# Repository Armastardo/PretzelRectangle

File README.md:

# PretzelRectangle
Custom rectangle PCB for PretzelGuy

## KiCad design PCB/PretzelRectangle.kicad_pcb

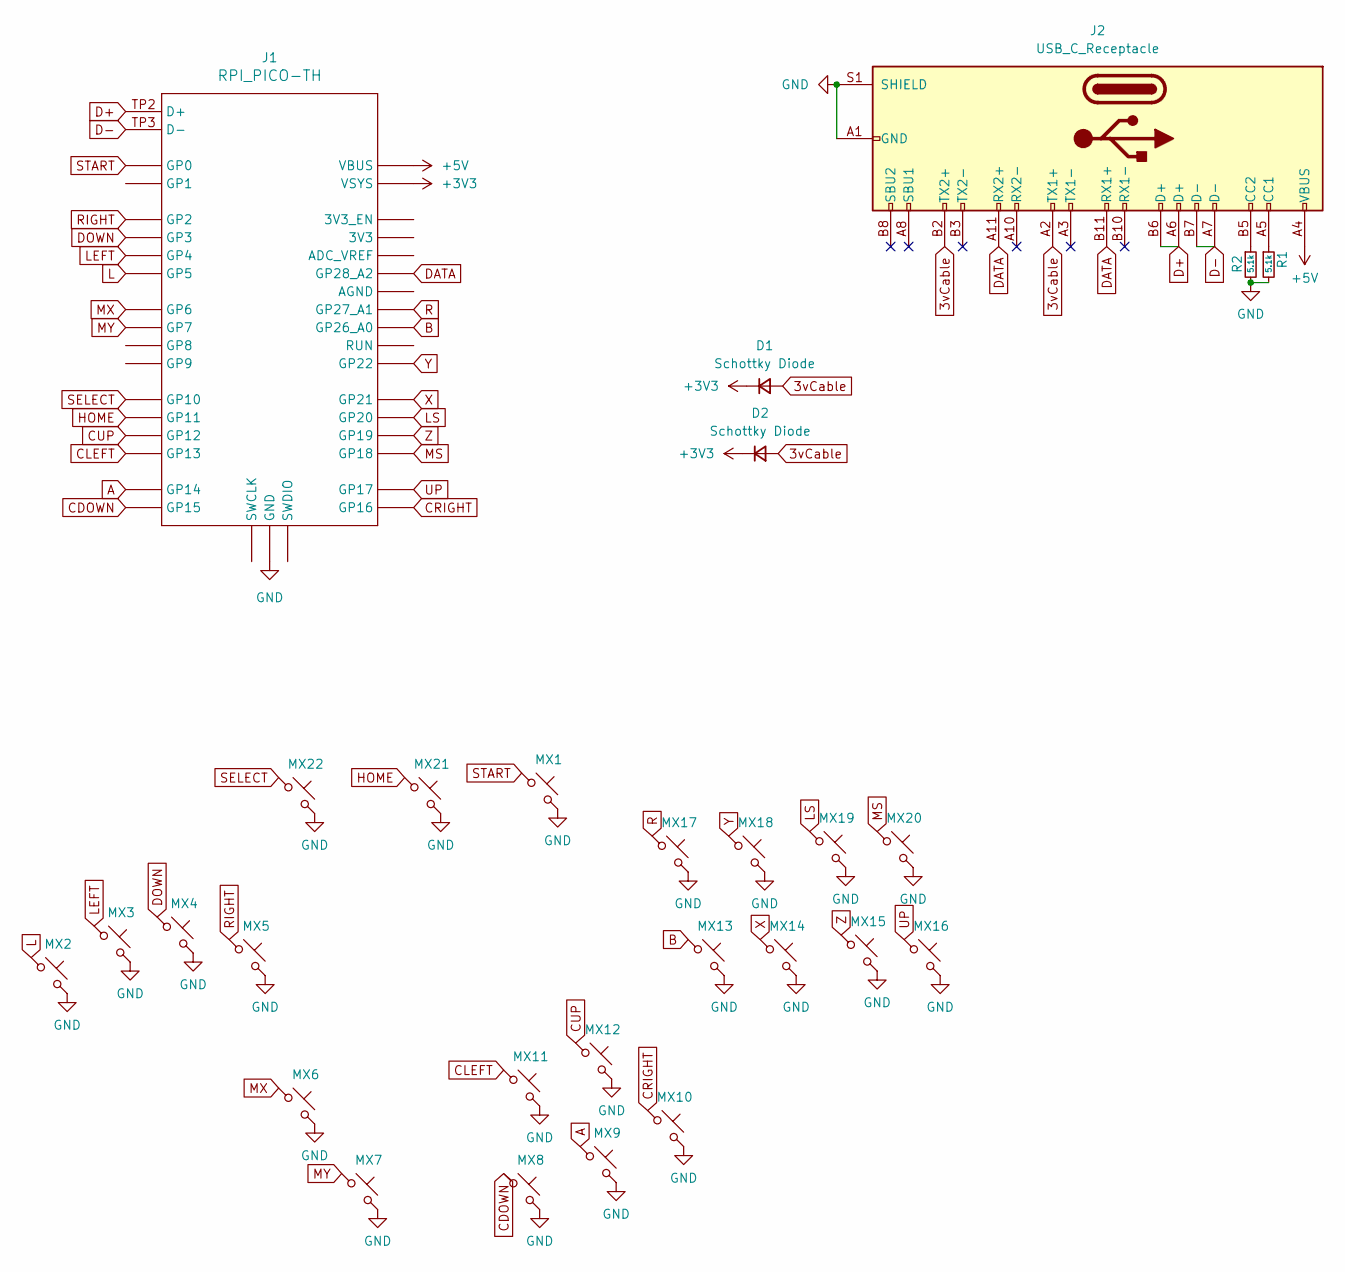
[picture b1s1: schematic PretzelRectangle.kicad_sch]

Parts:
D1: Schottky Diode; D_SOD-123; LCSC C8598
D2: Schottky Diode; D_DO-201AD_P15.24mm_Horizontal
J1: RPI_PICO-TH; RPI_PICO_TH
J2: USB_C_Receptacle; TYPE-C_24P_QCHT; LCSC C456013
MX1, MX2, MX3, MX4, MX5, MX6, MX7, MX8, MX9, MX10, MX11, MX12, MX13, MX14, MX15, MX16, MX17, MX18, MX19, MX20, MX21, MX22: MX_SW_HS; SW_MX_HS_1u
R1, R2: 5.1k; LED_0805_2012Metric_Pad1.15x1.40mm_HandSolder

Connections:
3vCable: D1.2 (A), D2.2 (A), J2.A2 (TX1+), J2.B2 (TX2+)
+3V3: D1.1 (K), D2.1 (K), J1.VSYS
+5V: J1.VBUS, J2.A4 (VBUS), J2.A9 (VBUS), J2.B4 (VBUS), J2.B9 (VBUS)
A: J1.GP14, MX9.1
B: J1.GP26_A0, MX13.1
CDOWN: J1.GP15, MX8.1
CLEFT: J1.GP13, MX11.1
CRIGHT: J1.GP16, MX10.1
CUP: J1.GP12, MX12.1
D+: J1.TP2 (D+), J2.A6 (D+), J2.B6 (D+)
D-: J1.TP3 (D-), J2.A7 (D-), J2.B7 (D-)
DATA: J1.GP28_A2, J2.A11 (RX2+), J2.B11 (RX1+)
DOWN: J1.GP3, MX4.1
GND: J1.GND@1 (GND), J1.GND@2 (GND), J1.GND@3 (GND), J1.GND@4 (GND), J1.GND@5 (GND), J1.GND@6 (GND), J1.GND@7 (GND), J1.GND@8 (GND), J2.A1 (GND), J2.A12 (GND), J2.B1 (GND), J2.B12 (GND), J2.S1 (SHIELD), MX1.2, MX2.2, MX3.2, MX4.2, MX5.2, MX6.2, MX7.2, MX8.2, MX9.2, MX10.2, MX11.2, MX12.2, MX13.2, MX14.2, MX15.2, MX16.2, MX17.2, MX18.2, MX19.2, MX20.2, MX21.2, MX22.2, R1.2, R2.2
HOME: J1.GP11, MX21.1
L: J1.GP5, MX2.1
LEFT: J1.GP4, MX3.1
LS: J1.GP20, MX19.1
MS: J1.GP18, MX20.1
MX: J1.GP6, MX6.1
MY: J1.GP7, MX7.1
unnamed: J2.A5 (CC1), R1.1
unnamed: J2.B5 (CC2), R2.1
R: J1.GP27_A1, MX17.1
RIGHT: J1.GP2, MX5.1
SELECT: J1.GP10, MX22.1
START: J1.GP0, MX1.1
UP: J1.GP17, MX16.1
X: J1.GP21, MX14.1
Y: J1.GP22, MX18.1
Z: J1.GP19, MX15.1

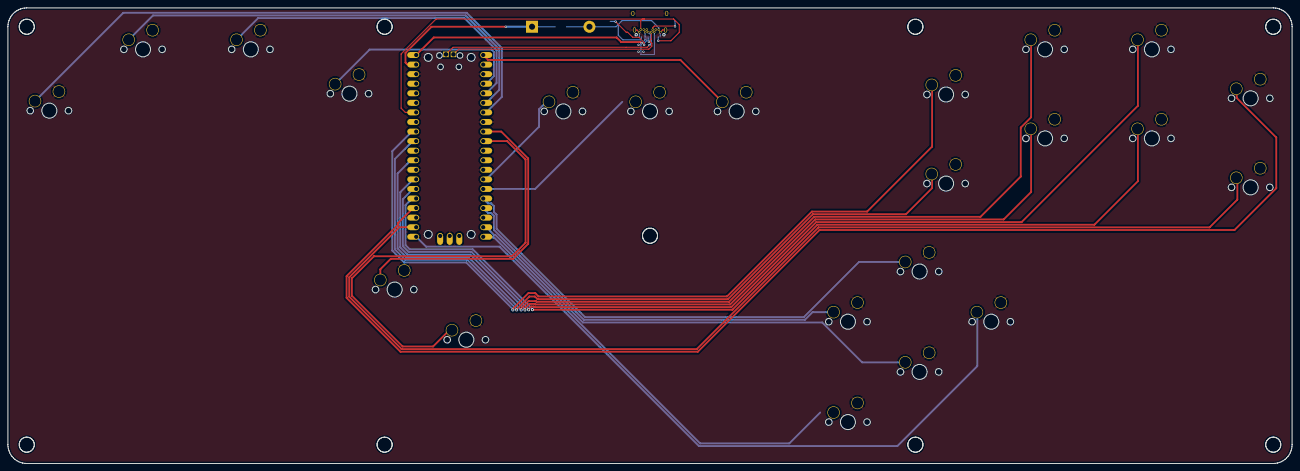
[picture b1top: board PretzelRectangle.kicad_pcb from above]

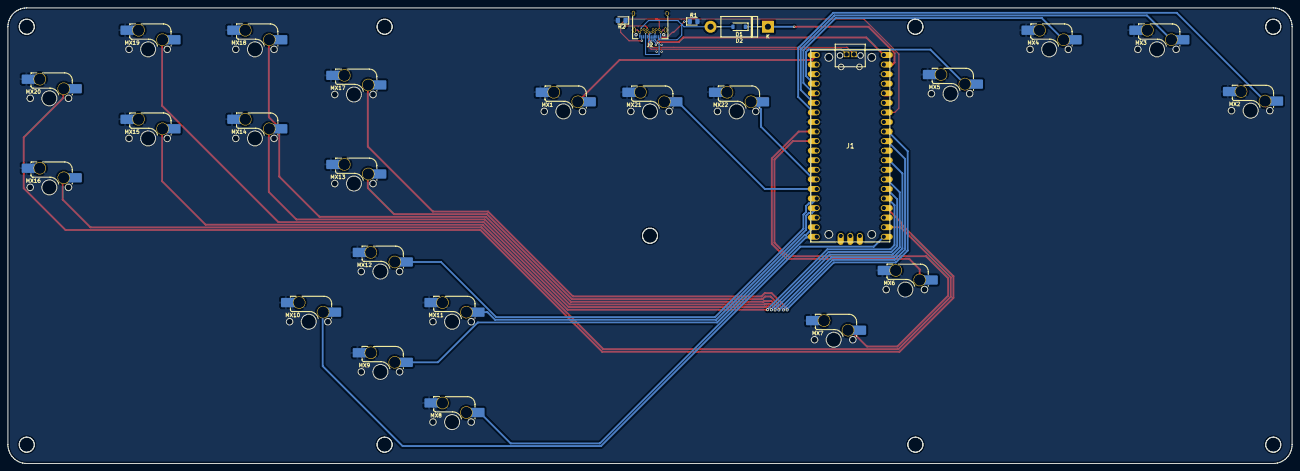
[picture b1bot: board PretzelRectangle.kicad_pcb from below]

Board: 2 copper layers, 340.9 x 120.9 mm, 28 parts (28 on the bottom side), 31 nets.

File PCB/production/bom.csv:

Designator,Footprint,Quantity,Value,LCSC Part #
D1,D_SOD-123,1,Schottky Diode,
D2,D_DO-201AD_P15.24mm_Horizontal,1,Schottky Diode,
J1,RPI_PICO_TH,1,RPI_PICO-TH,
J2,TYPE-C_24P_QCHT,1,USB_C_Receptacle,
"MX1, MX10, MX11, MX12, MX13, MX14, MX15, MX16, MX17, MX18, MX19, MX2, MX20, MX21, MX22, MX3, MX4, MX5, MX6, MX7, MX8, MX9",SW_MX_HS_1u,22,MX_SW_HS,
"R1, R2",0805,2,5.1k,

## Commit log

2023-07-19 Finished first version
